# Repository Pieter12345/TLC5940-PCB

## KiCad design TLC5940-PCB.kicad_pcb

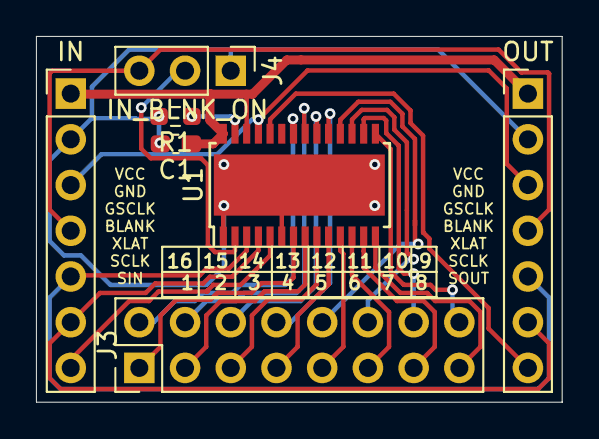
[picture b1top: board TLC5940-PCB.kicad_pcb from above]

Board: 2 copper layers, 29.2 x 20.3 mm, 7 parts (0 on the bottom side), 26 nets.

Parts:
C1: C_Small; C_0603_1608Metric_Pad1.08x0.95mm_HandSolder
IN: Conn_01x07_Male; PinHeader_1x07_P2.54mm_Vertical
J3: Conn_02x08_Counter_Clockwise; PinHeader_2x08_P2.54mm_Vertical_Clockwise
J4: Conn_01x03_Male; PinHeader_1x03_P2.54mm_Vertical
OUT: Conn_01x07_Male; PinHeader_1x07_P2.54mm_Vertical
R1: R_Small_US; R_0603_1608Metric_Pad0.98x0.95mm_HandSolder
U1: TLC5940PWP; HTSSOP-28-1EP_4.4x9.7mm_P0.65mm_EP3.4x9.5mm

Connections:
GND: C1.2, IN.2, J4.1, OUT.2, R1.2, U1.1, U1.6, U1.29
unnamed: IN.3, OUT.3, U1.25
unnamed: IN.4, J4.3, OUT.4
unnamed: IN.5, OUT.5, U1.3
unnamed: IN.6, OUT.6, U1.4
unnamed: IN.7, U1.5
unnamed: J3.1, U1.7
unnamed: J3.2, U1.8
unnamed: J3.3, U1.9
unnamed: J3.4, U1.10
unnamed: J3.5, U1.11
unnamed: J3.6, U1.12
unnamed: J3.7, U1.13
unnamed: J3.8, U1.14
unnamed: J3.9, U1.15
unnamed: J3.10, U1.16
unnamed: J3.11, U1.17
unnamed: J3.12, U1.18
unnamed: J3.13, U1.19
unnamed: J3.14, U1.20
unnamed: J3.15, U1.21
unnamed: J3.16, U1.22
unnamed: J4.2, U1.2
unnamed: OUT.7, U1.24
unnamed: R1.1, U1.27
VCC: C1.1, IN.1, OUT.1, U1.26, U1.28

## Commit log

2021-05-25 Move files one directory down
2021-05-26 Update resistor/capacitor footprints
    These were 0201_0603 instead of 0603_1608.
2021-05-26 Move traces around + add ground plane
2021-05-26 Move cap closer to TLC VCC + Decrease via size
